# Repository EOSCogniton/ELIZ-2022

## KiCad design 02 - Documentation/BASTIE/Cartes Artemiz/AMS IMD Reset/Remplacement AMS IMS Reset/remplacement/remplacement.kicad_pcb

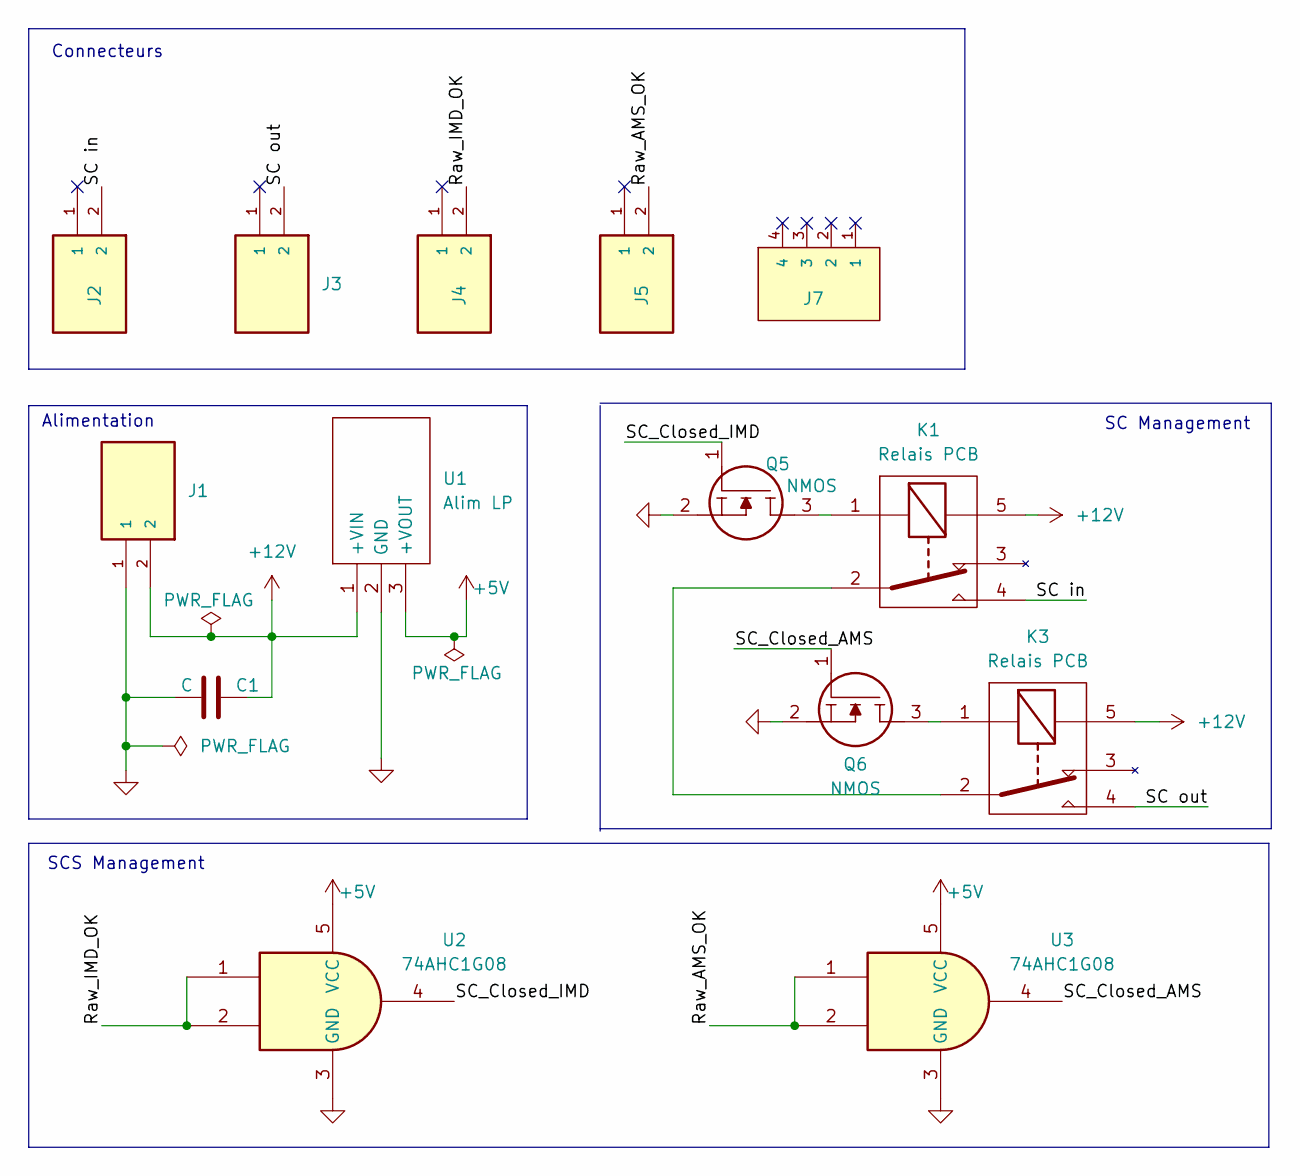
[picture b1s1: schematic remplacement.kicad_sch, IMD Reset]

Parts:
C1: C; CP_Radial_D5.0mm_P2.00mm
J1, J2, J3, J4, J5: 2P Droit 2-11-2022; MOLEX_22-11-2022; PARTREV BD8; Mouser Part Number 538-22-11-2022
J7: 4P Droit 22-11-2042; MOLEX_22-11-2042; Manufacturer_Part_Number 22-11-2042; Mouser Part Number 538-22-11-2042
K1, K3: Relais PCB; CP112V; Mouser Part Number 769-CP1-12V
Q5, Q6: NMOS SQ2348ES-T1_GE3; SOT95P237X112-3N; Manufacturer_Part_Number SQ2348ES-T1_GE3; Mouser Part Number 781-SQ2348ES-T1_GE3
U1: Alim LP TSR_0.5-2450; TSR-0.5-2433; Manufacturer_Part_Number TSR 0.5-2450; Mouser Part Number 495-TSR0.5-2450
U2, U3: 74AHC1G08; SOT-23-5_L3.0-W1.7-P0.95-LS2.8-BL

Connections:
+5V: U1.3 (+VOUT), U2.5 (VCC), U3.5 (VCC)
+12V: C1.2, J1.2, K1.5, K3.5, U1.1 (+VIN)
/Raw_AMS_OK: J5.2, U3.1, U3.2
/Raw_IMD_OK: J4.2, U2.1, U2.2
/SC in: J2.2, K1.4
/SC out: J3.2, K3.4
/SC_Closed_AMS: Q6.1, U3.4
/SC_Closed_IMD: Q5.1, U2.4
GND: C1.1, J1.1, Q5.2, Q6.2, U1.2 (GND), U2.3 (GND), U3.3 (GND)
unnamed: K1.1, Q5.3
unnamed: K1.2, K3.2
unnamed: K3.1, Q6.3

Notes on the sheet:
Alimentation
SC Management
SCS Management
Connecteurs

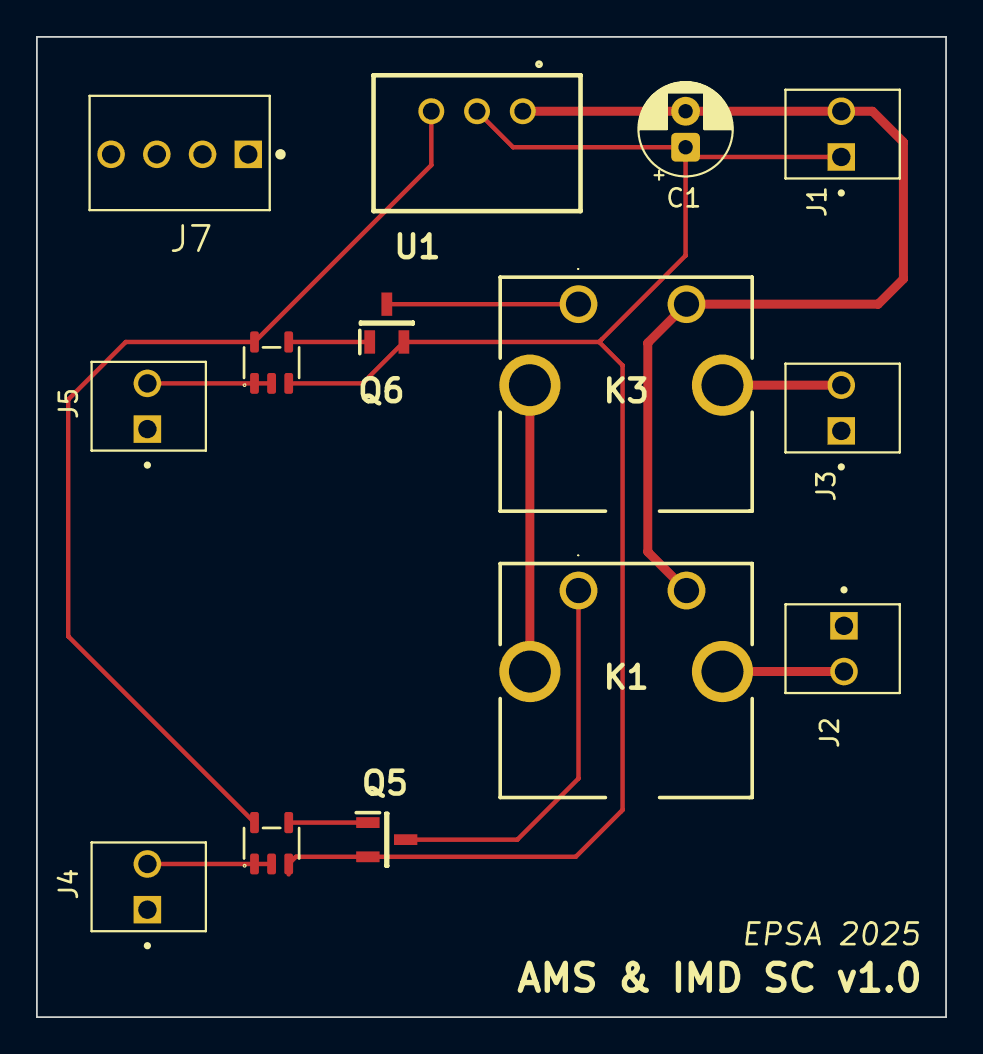
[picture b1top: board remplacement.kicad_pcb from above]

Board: 2 copper layers, 50.5 x 54.5 mm, 14 parts (0 on the bottom side), 12 nets.

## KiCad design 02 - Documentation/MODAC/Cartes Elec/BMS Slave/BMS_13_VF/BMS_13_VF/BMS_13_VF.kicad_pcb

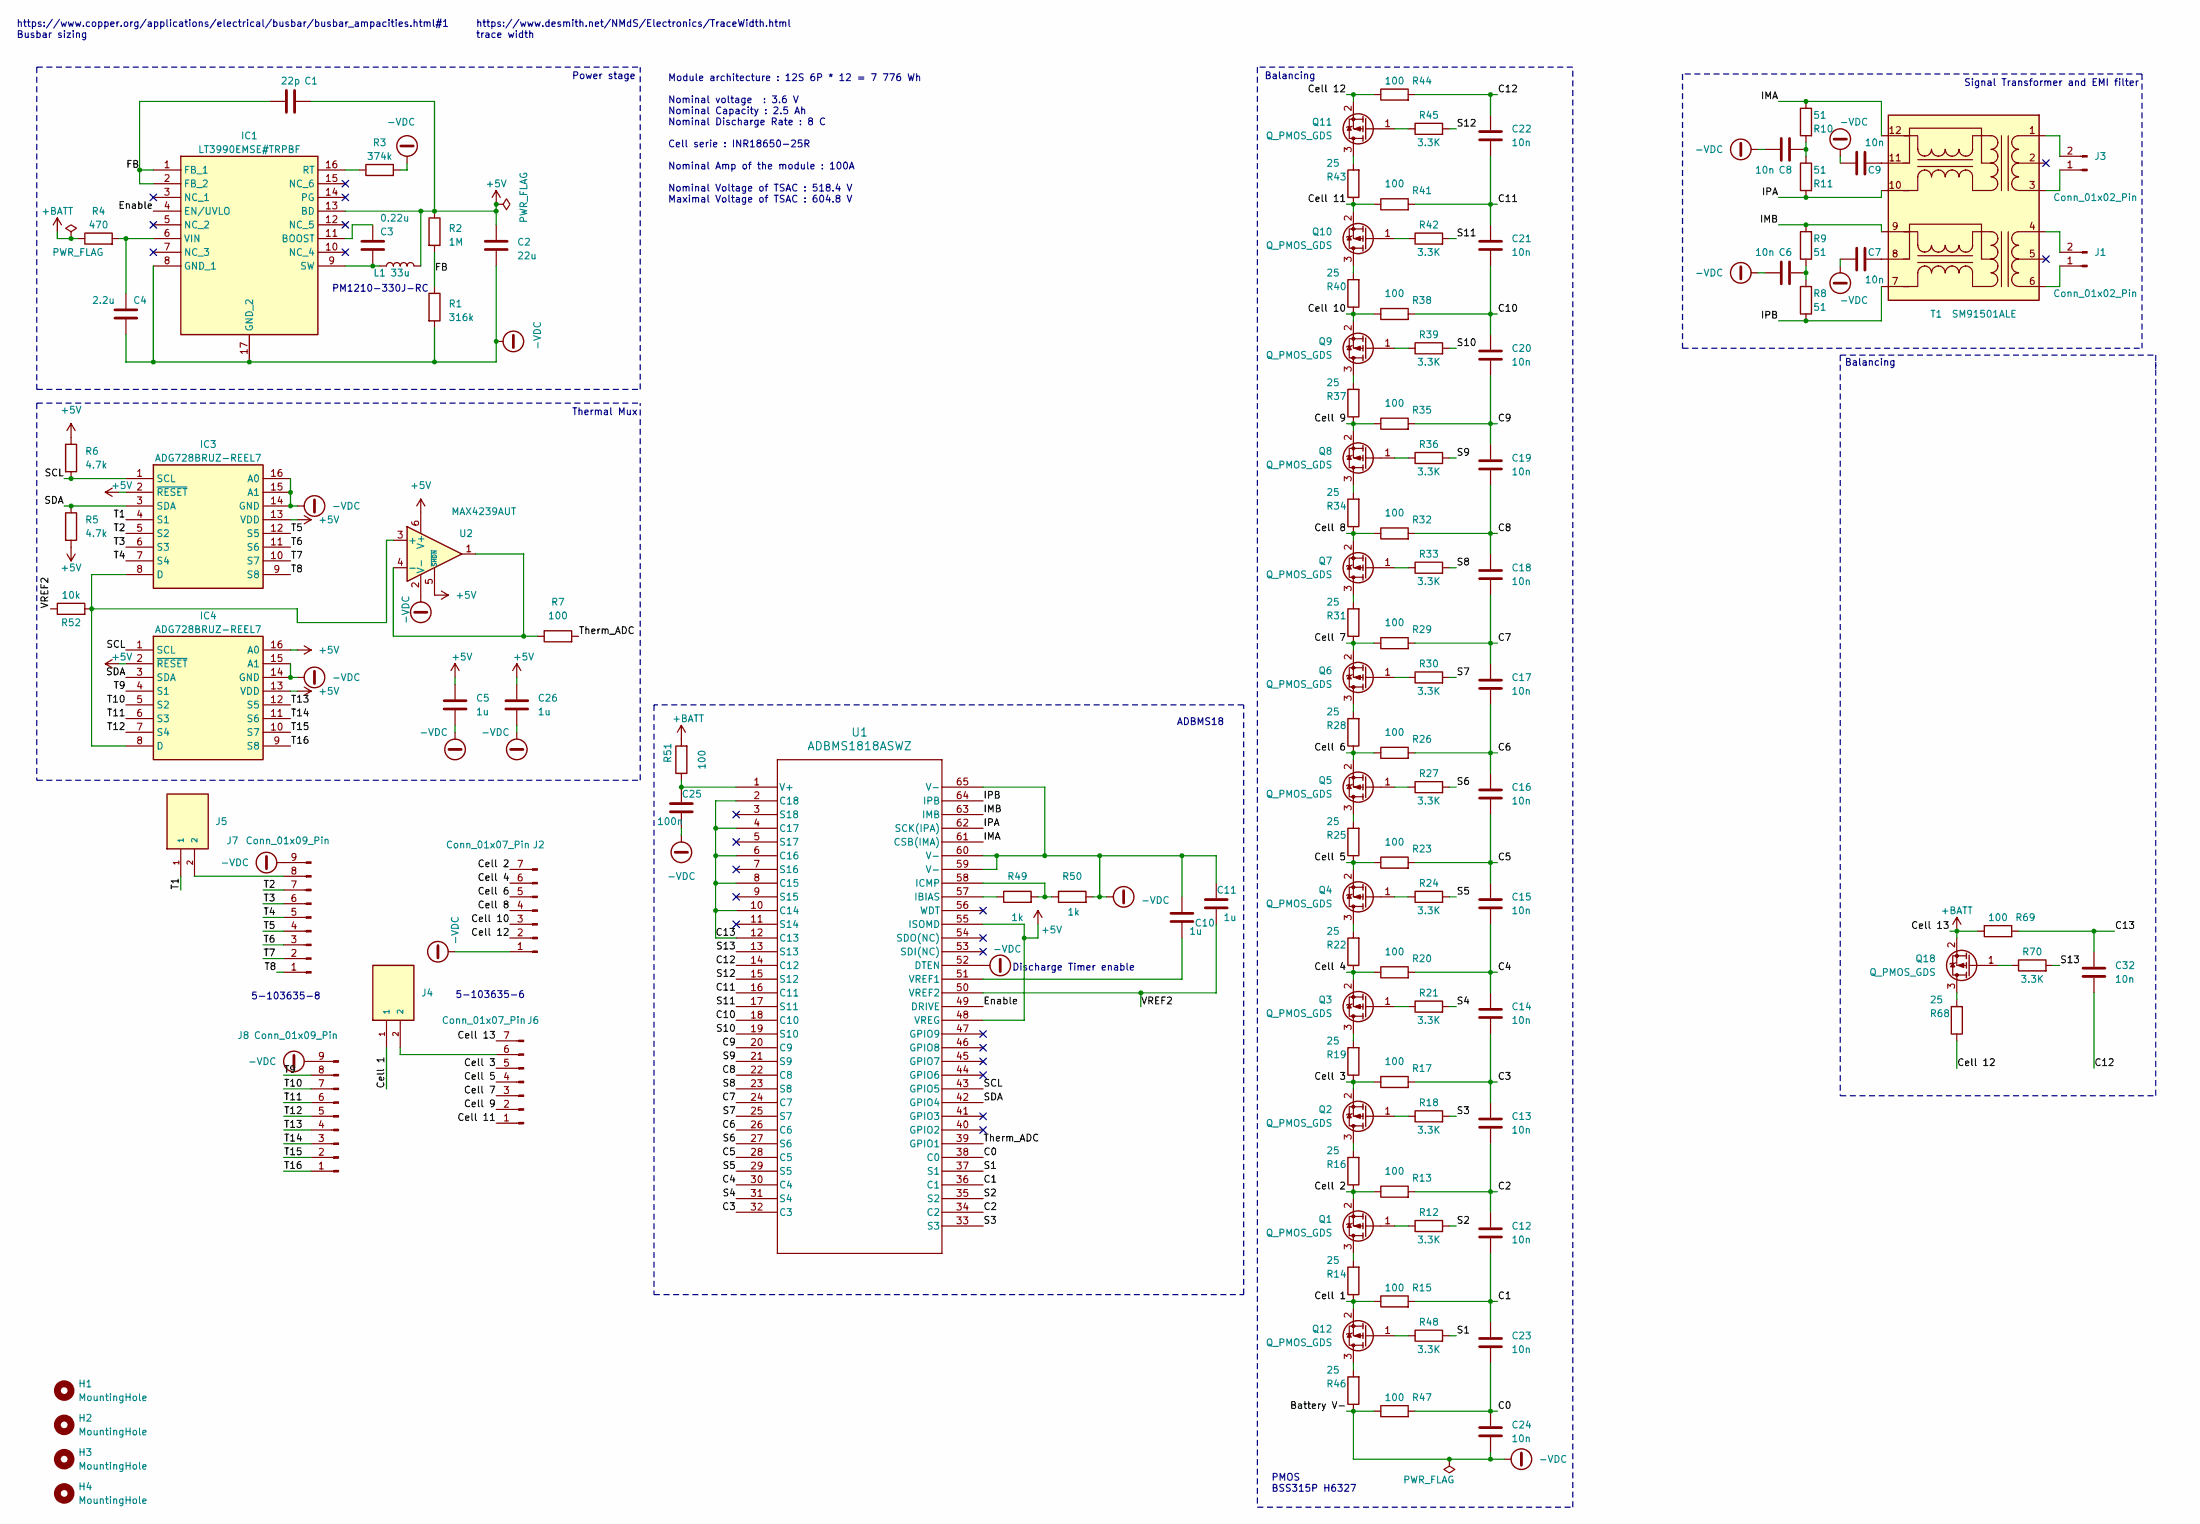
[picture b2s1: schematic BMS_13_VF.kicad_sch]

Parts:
C1: 22p; C_0805_2012Metric_Pad1.18x1.45mm_HandSolder
C2: 22u; C_0805_2012Metric_Pad1.18x1.45mm_HandSolder
C3: 0.22u; C_0805_2012Metric_Pad1.18x1.45mm_HandSolder
C4: 2.2u; C_0805_2012Metric_Pad1.18x1.45mm_HandSolder
C5, C10, C11, C26: 1u; C_0805_2012Metric_Pad1.18x1.45mm_HandSolder
C6, C7, C8, C9, C12, C13, C14, C15, C16, C17, C18, C19, C20, C21, C22, C23, C24, C32: 10n; C_0805_2012Metric_Pad1.18x1.45mm_HandSolder
C25: 100n; C_0805_2012Metric_Pad1.18x1.45mm_HandSolder
H1, H2, H3, H4: MountingHole; MountingHole_3.2mm_M3_DIN965_Pad
IC1: LT3990EMSE#TRPBF; SOP50P490X110-17N; Mouser Part Number 584-LT3990EMSE#TRPBF
IC3, IC4: ADG728BRUZ-REEL7; SOP65P640X120-16N; Mouser Part Number 584-ADG728BRUZ-R7
J1, J3: Conn_01x02_Pin; RHDR2W97P0X254_1X2_654X508X1379P
J2, J6: Conn_01x07_Pin; SHDRRA7W77P0X254_1X7_2032X1359X699P
J4, J5: 2P Droit 22-11-2022; MOLEX_22-11-2022; PARTREV BD8; Mouser Part Number 538-22-11-2022
J7, J8: Conn_01x09_Pin; SHDRRA9W69P0X254_1X9_2527X1359X741P
L1: 33u; L_1210_3225Metric_Pad1.42x2.65mm_HandSolder
Q1, Q2, Q3, Q4, Q5, Q6, Q7, Q8, Q9, Q10, Q11, Q12: Q_PMOS_GDS; SOT-23-3
Q18: Q_PMOS_GDS; SOT95P237X112-3N
R1: 316k; R_1206_3216Metric_Pad1.30x1.75mm_HandSolder
R2: 1M; R_1206_3216Metric_Pad1.30x1.75mm_HandSolder
R3: 374k; R_1206_3216Metric_Pad1.30x1.75mm_HandSolder
R4: 470; R_1206_3216Metric_Pad1.30x1.75mm_HandSolder
R5, R6: 4.7k; R_1206_3216Metric_Pad1.30x1.75mm_HandSolder
R7, R13, R15, R17, R20, R23, R26, R29, R32, R35, R38, R41, R44, R47, R51, R69: 100; R_1206_3216Metric_Pad1.30x1.75mm_HandSolder
R8, R9, R10, R11: 51; R_1206_3216Metric_Pad1.30x1.75mm_HandSolder
R12, R18, R21, R24, R27, R30, R33, R36, R39, R42, R45, R48, R70: 3.3K; R_1206_3216Metric_Pad1.30x1.75mm_HandSolder
R14, R16, R19, R22, R25, R28, R31, R34, R37, R40, R43, R46, R68: 25; R_2512_6332Metric_Pad1.40x3.35mm_HandSolder
R49, R50: 1k; R_1206_3216Metric_Pad1.30x1.75mm_HandSolder
R52: 10k; R_1206_3216Metric_Pad1.30x1.75mm_HandSolder
T1: SM91501ALE; SOP200P1473X500-12N; Mouser Part Number 652-SM91501ALE
U1: ADBMS1818ASWZ; 05-08-1982_ADI
U2: MAX4239AUT; SOT-23-6

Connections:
+5V: C1.2, C2.2, C5.1, C26.1, IC1.13 (BD), IC3.2 (~RESET), IC3.13 (VDD), IC4.2 (~RESET), IC4.13 (VDD), IC4.16 (A0), L1.2, R2.1, R5.2, R6.1, U1.48 (VREG), U1.55 (ISOMD), U2.5 (~SHDN), U2.6 (V+)
+BATT: J6.7, Q18.2 (S), R4.1, R51.2, R69.1
-VDC: C2.1, C4.1, C5.2, C6.1, C7.1, C8.1, C9.1, C10.1, C11.1, C24.2, C25.2, C26.2, IC1.8 (GND_1), IC1.17 (GND_2), IC3.14 (GND), IC3.15 (A1), IC3.16 (A0), IC4.14 (GND), IC4.15 (A1), J2.1, J7.9, J8.9, R1.2, R3.2, R46.1, R47.1, R50.2, U1.52 (DTEN), U1.59 (V-), U1.60 (V-), U1.65 (V-), U2.2 (V-)
/C0: C23.2, C24.1, R47.2, U1.38 (C0)
/C1: C12.2, C23.1, R15.2, U1.36 (C1)
/C2: C12.1, C13.2, R13.2, U1.34 (C2)
/C3: C13.1, C14.2, R17.2, U1.32 (C3)
/C4: C14.1, C15.2, R20.2, U1.30 (C4)
/C5: C15.1, C16.2, R23.2, U1.28 (C5)
/C6: C16.1, C17.2, R26.2, U1.26 (C6)
/C7: C17.1, C18.2, R29.2, U1.24 (C7)
/C8: C18.1, C19.2, R32.2, U1.22 (C8)
/C9: C19.1, C20.2, R35.2, U1.20 (C9)
/C10: C20.1, C21.2, R38.2, U1.18 (C10)
/C11: C21.1, C22.2, R41.2, U1.16 (C11)
/C12: C22.1, C32.2, R44.2, U1.14 (C12)
/C13: C32.1, R69.2, U1.2 (C18), U1.4 (C17), U1.6 (C16), U1.8 (C15), U1.10 (C14), U1.12 (C13)
/Cell 1: J4.1, Q12.2 (S), R14.1, R15.1
/Cell 2: J2.7, Q1.2 (S), R13.1, R16.1
/Cell 3: J6.5, Q2.2 (S), R17.1, R19.1
/Cell 4: J2.6, Q3.2 (S), R20.1, R22.1
/Cell 5: J6.4, Q4.2 (S), R23.1, R25.1
/Cell 6: J2.5, Q5.2 (S), R26.1, R28.1
/Cell 7: J6.3, Q6.2 (S), R29.1, R31.1
/Cell 8: J2.4, Q7.2 (S), R32.1, R34.1
/Cell 9: J6.2, Q8.2 (S), R35.1, R37.1
/Cell 10: J2.3, Q9.2 (S), R38.1, R40.1
/Cell 11: J6.1, Q10.2 (S), R41.1, R43.1
/Cell 12: J2.2, Q11.2 (S), R44.1, R68.1
/Enable: IC1.4 (EN/UVLO), U1.49 (DRIVE)
/FB: C1.1, IC1.1 (FB_1), IC1.2 (FB_2), R1.1, R2.2
/IMA: R10.1, T1.12 (SEC1_3), U1.61 (CSB(IMA))
/IMB: R9.2, T1.9 (SEC2_3), U1.63 (IMB)
/IPA: R11.2, T1.10 (SEC1_1), U1.62 (SCK(IPA))
/IPB: R8.1, T1.7 (SEC2_1), U1.64 (IPB)
/S1: R48.2, U1.37 (S1)
/S2: R12.2, U1.35 (S2)
/S3: R18.2, U1.33 (S3)
/S4: R21.2, U1.31 (S4)
/S5: R24.2, U1.29 (S5)
/S6: R27.2, U1.27 (S6)
/S7: R30.2, U1.25 (S7)
/S8: R33.2, U1.23 (S8)
/S9: R36.2, U1.21 (S9)
/S10: R39.2, U1.19 (S10)
/S11: R42.2, U1.17 (S11)
/S12: R45.2, U1.15 (S12)
/S13: R70.2, U1.13 (S13)
/SCL: IC3.1 (SCL), IC4.1 (SCL), R6.2, U1.43 (GPIO5)
/SDA: IC3.3 (SDA), IC4.3 (SDA), R5.1, U1.42 (GPIO4)
/T1: IC3.4 (S1), J5.1
/T2: IC3.5 (S2), J7.7
/T3: IC3.6 (S3), J7.6
/T4: IC3.7 (S4), J7.5
/T5: IC3.12 (S5), J7.4
/T6: IC3.11 (S6), J7.3
/T7: IC3.10 (S7), J7.2
/T8: IC3.9 (S8), J7.1
/T9: IC4.4 (S1), J8.8
/T10: IC4.5 (S2), J8.7
/T11: IC4.6 (S3), J8.6
/T12: IC4.7 (S4), J8.5
/T13: IC4.12 (S5), J8.4
/T14: IC4.11 (S6), J8.3
/T15: IC4.10 (S7), J8.2
/T16: IC4.9 (S8), J8.1
/Therm_ADC: R7.2, U1.39 (GPIO1)
/VREF2: C11.2, R52.1, U1.50 (VREF2)
unnamed: C6.2, R8.2, R9.1
unnamed: C8.2, R10.2, R11.1
unnamed: C3.2, IC1.11 (BOOST)
unnamed: IC1.16 (RT), R3.1
unnamed: C3.1, IC1.9 (SW), L1.1
unnamed: C4.2, IC1.6 (VIN), R4.2
unnamed: IC3.8 (D), IC4.8 (D), R52.2, U2.3 (+)
unnamed: J1.1, T1.6 (PRI2_3)
unnamed: J1.2, T1.4 (PRI2_1)
unnamed: J3.1, T1.3 (PRI1_3)
unnamed: J3.2, T1.1 (PRI1_1)
unnamed: J4.2, J6.6
unnamed: J5.2, J7.8
unnamed: Q1.3 (D), R14.2
unnamed: Q1.1 (G), R12.1
unnamed: Q2.3 (D), R16.2
unnamed: Q2.1 (G), R18.1
unnamed: Q3.3 (D), R19.2
unnamed: Q3.1 (G), R21.1
unnamed: Q4.3 (D), R22.2
unnamed: Q4.1 (G), R24.1
unnamed: Q5.3 (D), R25.2
unnamed: Q5.1 (G), R27.1
unnamed: Q6.3 (D), R28.2
unnamed: Q6.1 (G), R30.1
unnamed: Q7.3 (D), R31.2
unnamed: Q7.1 (G), R33.1
unnamed: Q8.3 (D), R34.2
unnamed: Q8.1 (G), R36.1
unnamed: Q9.3 (D), R37.2
unnamed: Q9.1 (G), R39.1
unnamed: Q10.3 (D), R40.2
unnamed: Q10.1 (G), R42.1
unnamed: Q11.3 (D), R43.2
unnamed: Q11.1 (G), R45.1
unnamed: Q12.3 (D), R46.2
unnamed: Q12.1 (G), R48.1
unnamed: Q18.3 (D), R68.2
unnamed: Q18.1 (G), R70.1
unnamed: C9.2, T1.11 (SEC1_2)
unnamed: C7.2, T1.8 (SEC2_2)
unnamed: R49.1, U1.57 (IBIAS)
unnamed: R49.2, R50.1, U1.58 (ICMP)
unnamed: C25.1, R51.1, U1.1 (V+)
unnamed: C10.2, U1.51 (VREF1)
unnamed: R7.1, U2.1, U2.4 (-)

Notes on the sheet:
Module architecture : 12S 6P * 12 = 7 776 Wh Nominal voltage : 3.6 V Nominal Capacity : 2.5 Ah Nominal Discharge Rate : 8 C Cell serie : INR18650-25R Nominal Amp of the module : 100A Nominal Voltage of TSAC : 518.4 V Maximal Voltage of TSAC : 604.8 V
PMOS BSS315P H6327
PM1210-330J-RC
Balancing
Thermal Mux
Power stage
Signal Transformer and EMI filter
ADBMS18
https://www.desmith.net/NMdS/Electronics/TraceWidth.html trace width
5-103635-8
https://www.copper.org/applications/electrical/busbar/busbar_ampacities.html#1 Busbar sizing
5-103635-6
Discharge Timer enable

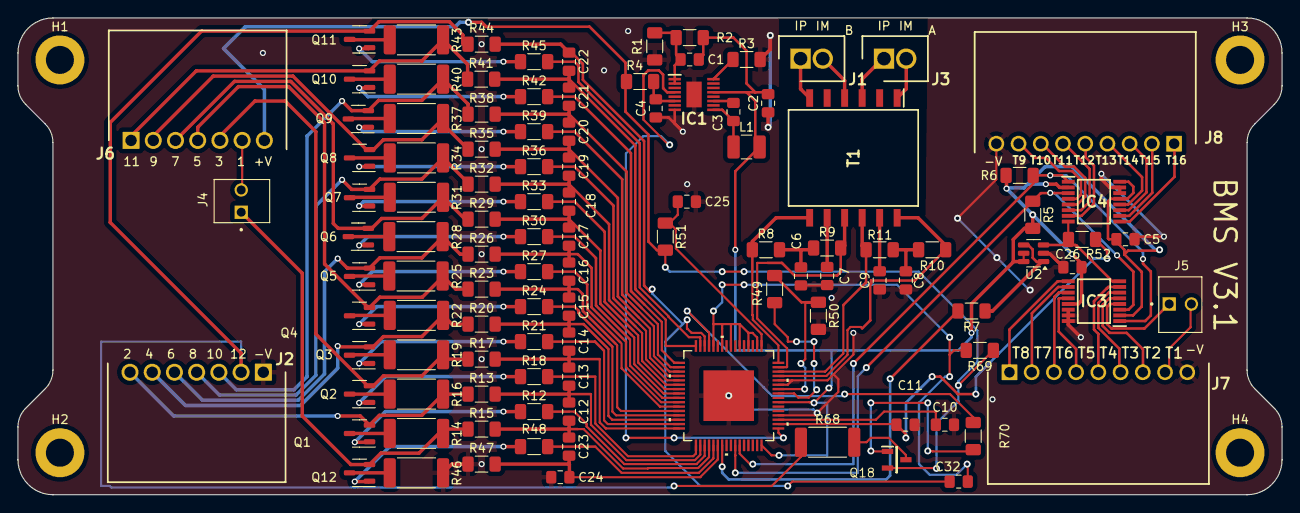
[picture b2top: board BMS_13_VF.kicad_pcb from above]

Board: 2 copper layers, 144.5 x 54.5 mm, 114 parts (0 on the bottom side), 114 nets.

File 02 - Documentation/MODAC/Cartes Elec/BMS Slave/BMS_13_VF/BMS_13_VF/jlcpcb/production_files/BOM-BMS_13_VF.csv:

Comment,Designator,Footprint,LCSC,Quantity
Q_PMOS_GDS,"Q1,Q10,Q11,Q12,Q18,Q2,Q3,Q4,Q5,Q6,Q7,Q8,Q9",SOT-23-3,C10487,13
25,"R14,R16,R19,R22,R25,R28,R31,R34,R37,R40,R43,R46,R68",R_2512_6332Metric_Pad1.40x3.35mm_HandSolder,C107659,13
10n,"C12,C13,C14,C15,C16,C17,C18,C19,C20,C21,C22,C23,C24,C32,C6,C7,C8,C9",C_0805_2012Metric_Pad1.18x1.45mm_HandSolder,C1710,18
100,"R13,R15,R17,R20,R23,R26,R29,R32,R35,R38,R41,R44,R47,R51,R69,R7",R_1206_3216Metric_Pad1.30x1.75mm_HandSolder,C17901,16
10k,R52,R_1206_3216Metric_Pad1.30x1.75mm_HandSolder,C17902,1
1M,R2,R_1206_3216Metric_Pad1.30x1.75mm_HandSolder,C17927,1
4.7k,"R5,R6",R_1206_3216Metric_Pad1.30x1.75mm_HandSolder,C17936,2
51,"R10,R11,R8,R9",R_1206_3216Metric_Pad1.30x1.75mm_HandSolder,C18019,4
22p,C1,C_0805_2012Metric_Pad1.18x1.45mm_HandSolder,C1804,1
316k,R1,R_1206_3216Metric_Pad1.30x1.75mm_HandSolder,C247297,1
33u,L1,L_1210_3225Metric_Pad1.42x2.65mm_HandSolder,C250234,1
3.3K,"R12,R18,R21,R24,R27,R30,R33,R36,R39,R42,R45,R48,R70",R_1206_3216Metric_Pad1.30x1.75mm_HandSolder,C26032,13
100n,C25,C_0805_2012Metric_Pad1.18x1.45mm_HandSolder,C28233,1
1u,"C10,C11,C26,C5",C_0805_2012Metric_Pad1.18x1.45mm_HandSolder,C28323,4
374k,R3,R_1206_3216Metric_Pad1.30x1.75mm_HandSolder,C2984514,1
ADBMS1818ASWZ,U1,05-08-1982_ADI,C3682393,1
2.2u,C4,C_0805_2012Metric_Pad1.18x1.45mm_HandSolder,C377773,1
1k,"R49,R50",R_1206_3216Metric_Pad1.30x1.75mm_HandSolder,C4410,2
470,R4,R_1206_3216Metric_Pad1.30x1.75mm_HandSolder,C4502,1
22u,C2,C_0805_2012Metric_Pad1.18x1.45mm_HandSolder,C45783,1
MAX4239AUT,U2,SOT-23-6,C479740,1
0.22u,C3,C_0805_2012Metric_Pad1.18x1.45mm_HandSolder,C5378,1
ADG728BRUZ-REEL7,"IC3,IC4",SOP65P640X120-16N,C579101,2
LT3990EMSE#TRPBF,IC1,SOP50P490X110-17N,C580168,1
SM91501ALE,T1,SOP200P1473X500-12N,,1

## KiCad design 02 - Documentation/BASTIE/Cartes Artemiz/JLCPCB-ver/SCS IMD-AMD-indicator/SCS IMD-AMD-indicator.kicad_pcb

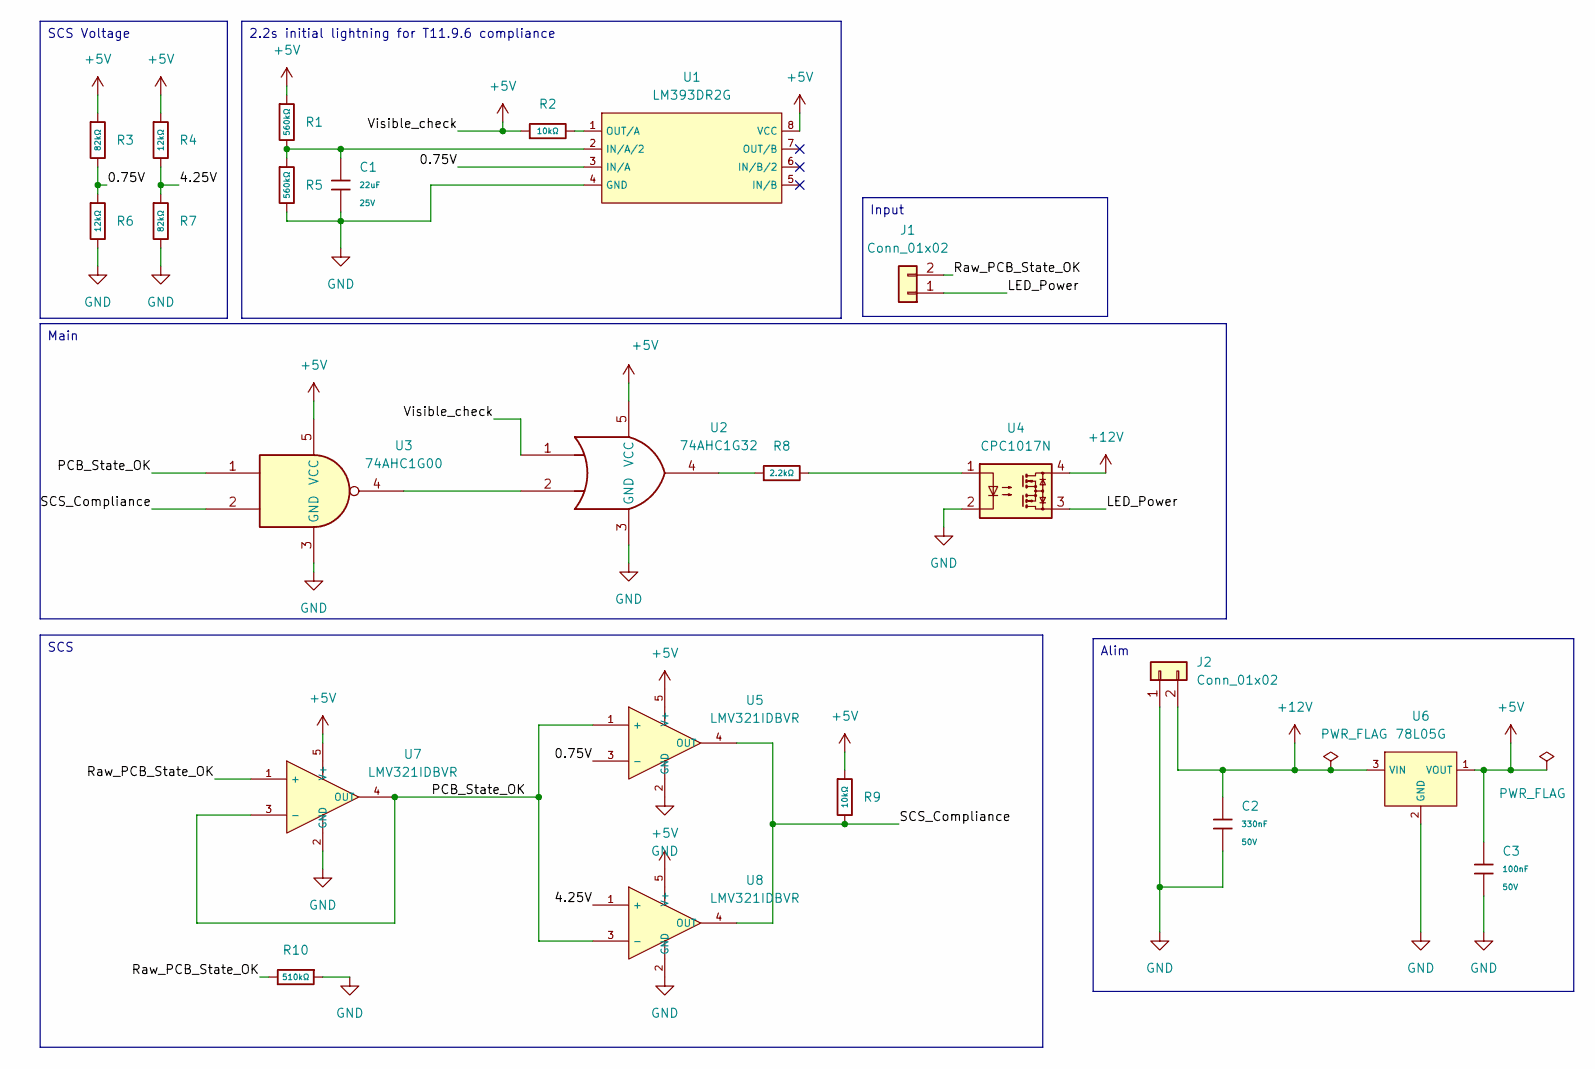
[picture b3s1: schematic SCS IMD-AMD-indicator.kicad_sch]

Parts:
C1: 22uF; C_0805; Voltage Rated 25V; Tolerance ±20%; Part CL21A226MAQNNNE; LCSC C45783
C2: 330nF; C_0805; Voltage Rated 50V; Tolerance ±10%; Part 0805B334K500NT; LCSC C1740
C3: 100nF; C_0805; Voltage Rated 50V; Tolerance ±10%; Part CC0805KRX7R9BB104; LCSC C49678
J1, J2: Conn_01x02; Molex_KK-254_AE-6410-02A_1x02_P2.54mm_Vertical
R1, R5: 560kΩ; R_0603; Overload Voltage (Max) 75V; Tolerance ±1%; Part 0603WAF5603T5E; LCSC C23203
R2, R9: 10kΩ; R_0805; Overload Voltage (Max) 150V; Tolerance ±1%; Part 0805W8F1002T5E; LCSC C17414
R3, R7: 82kΩ; R_0805; Overload Voltage (Max) 150V; Tolerance ±1%; Part 0805W8F8202T5E; LCSC C17840
R4, R6: 12kΩ; R_0805; Overload Voltage (Max) 150V; Tolerance ±1%; Part 0805W8F1202T5E; LCSC C17444
R8: 2.2kΩ; R_0805; Overload Voltage (Max) 150V; Tolerance ±1%; Part 0805W8F2201T5E; LCSC C17520
R10: 510kΩ; R_0805; Overload Voltage (Max) 150V; Tolerance ±1%; Part 0805W8F5103T5E; LCSC C17733
U1: LM393DR2G; SOIC-8_L5.0-W4.0-P1.27-LS6.0-BL; Supply Voltage 2V~36V;1V~18V; Part LM393DR2G; LCSC C7955
U2: 74AHC1G32; SC-74A-5_1.55x2.9mm_P0.95mm
U3: 74AHC1G00; SOT-23-5_L3.0-W1.7-P0.95-LS2.8-BR
U4: CPC1017N; SOP-4_3.8x4.1mm_P2.54mm
U5, U7, U8: LMV321IDBVR; SOT-23-5_L3.0-W1.7-P0.95-LS2.8-BR; Part LMV321IDBVR; LCSC C7972
U6: 78L05G; SOT-89-3_L4.5-W2.5-P1.50-LS4.2-BR; Output Voltage 5V; Dropout Voltage 1.7V@(40mA); Part 78L05G-AB3-R; LCSC C71136

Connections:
+5V: C3.1, R1.1, R2.1, R3.1, R4.1, R9.1, U1.8 (VCC), U2.1, U2.5 (VCC), U3.5 (VCC), U5.5 (V+), U6.1 (VOUT), U7.5 (V+), U8.5 (V+)
+12V: C2.1, J2.2, U4.4, U6.3 (VIN)
/0.75V: R3.2, R6.1, U1.3 (IN/A), U5.3 (-)
/4.25V: R4.2, R7.1, U8.1 (+)
/LED_Power: J1.1, U4.3
/PCB_State_OK: U3.1, U5.1 (+), U7.3 (-), U7.4 (OUT), U8.3 (-)
/Raw_PCB_State_OK: J1.2, R10.2, U7.1 (+)
/SCS_Compliance: R9.2, U3.2, U5.4 (OUT), U8.4 (OUT)
GND: C1.2, C2.2, C3.2, J2.1, R5.2, R6.2, R7.2, R10.1, U1.4 (GND), U2.3 (GND), U3.3 (GND), U4.2, U5.2 (GND), U6.2 (GND), U7.2 (GND), U8.2 (GND)
unnamed: R8.1, U2.4
unnamed: R8.2, U4.1
unnamed: C1.1, R1.2, R5.1, U1.2 (IN/A/2)
unnamed: R2.2, U1.1 (OUT/A)
unnamed: U2.2, U3.4

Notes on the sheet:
Main
Input
2.2s initial lightning for T11.9.6 compliance
SCS Voltage
Alim
SCS

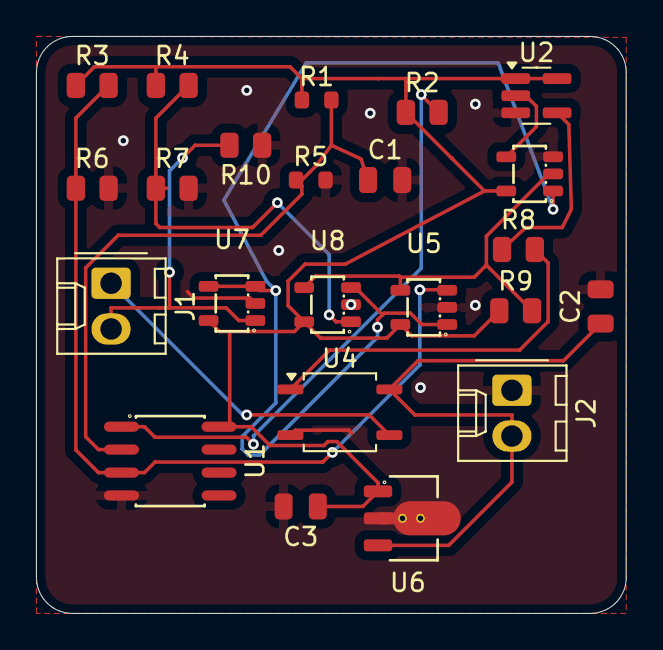
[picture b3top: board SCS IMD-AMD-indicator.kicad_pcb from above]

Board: 2 copper layers, 32.8 x 32.1 mm, 23 parts (0 on the bottom side), 14 nets.

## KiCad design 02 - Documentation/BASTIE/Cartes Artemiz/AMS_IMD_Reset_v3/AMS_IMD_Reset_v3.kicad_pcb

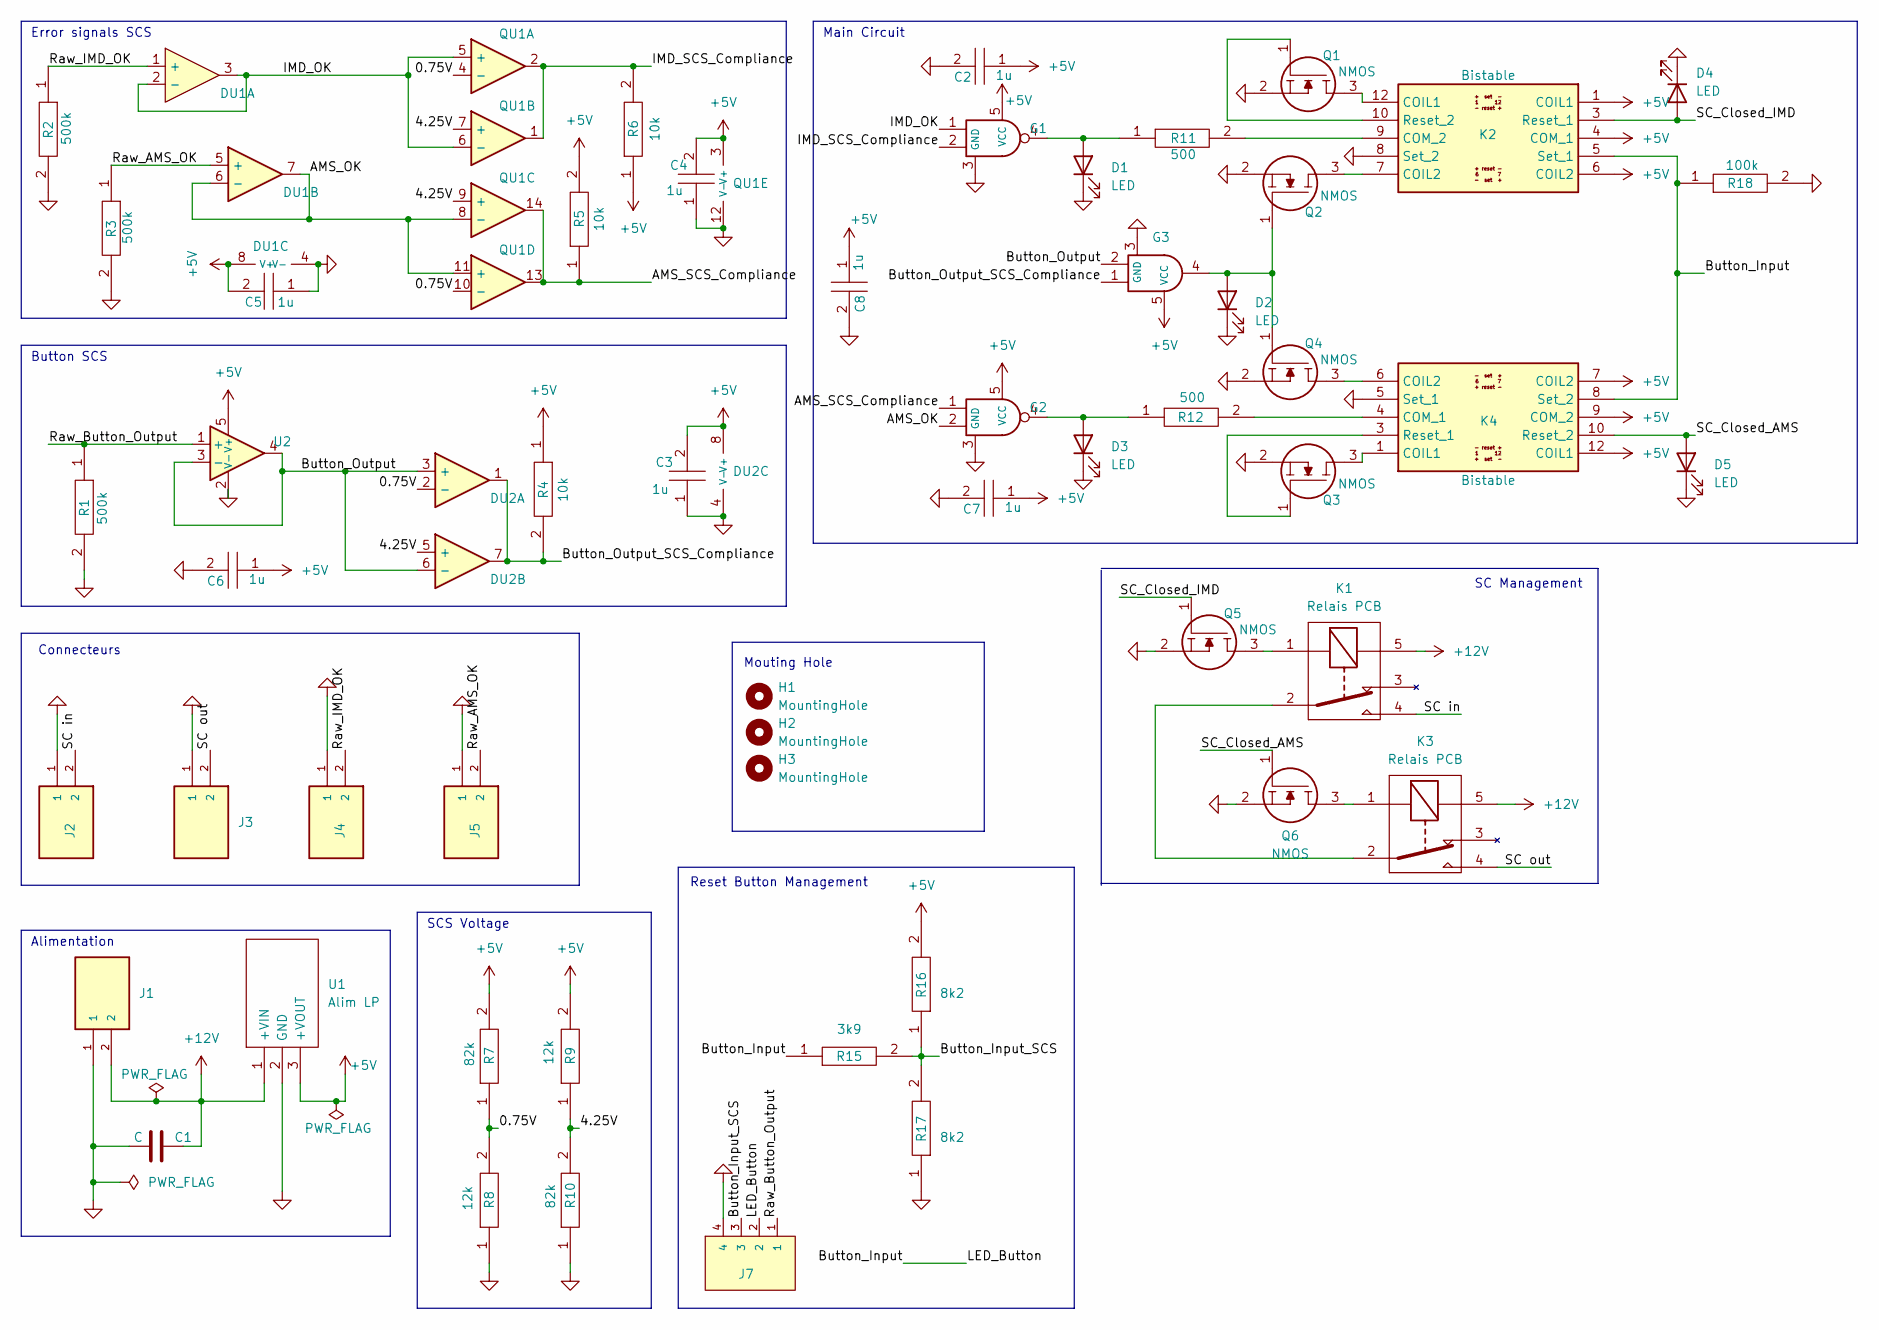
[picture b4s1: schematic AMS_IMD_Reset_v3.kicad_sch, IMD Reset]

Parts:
C1: C; CP_Radial_D5.0mm_P2.00mm
C2, C3, C4, C5, C6, C7, C8: 1u; CAPC2012X130N; Manufacturer_Part_Number 0805Y1000104JXT
D1, D2, D3, D4, D5: LED; LED_D5.0mm
DU1: Opamp_Dual; TSSOP-8_4.4x3mm_P0.65mm; Manufacturer_Part_Number TLV9062QPWRQ1; Mouser Part Number 595-TLV9062QPWRQ1
DU2: Opamp_Dual; TSSOP-8_4.4x3mm_P0.65mm; Manufacturer_Part_Number LMV393IPWR; Mouser Part Number 595-LMV393IPWR
G1, G2: Gate NAND SN74AHCT1G00DBVR; SOT95P280X145-5N; Manufacturer_Part_Number SN74AHCT1G00DBVR; Mouser Part Number 595-SN74AHCT1G00DBVR
G3: Gate AND SN74AHCT1G08DBVR; SOT95P280X145-5N; Manufacturer_Part_Number SN74AHCT1G08DBVR; Mouser Part Number 595-SN74AHCT1G08DBVR
H1, H2, H3: MountingHole; MountingHole_2.7mm_M2.5
J1, J2, J3, J4, J5: 2P Droit 2-11-2022; MOLEX_22-11-2022; PARTREV BD8; Mouser Part Number 538-22-11-2022
J7: 4P Droit 22-11-2042; MOLEX_22-11-2042; Manufacturer_Part_Number 22-11-2042; Mouser Part Number 538-22-11-2042
K1, K3: Relais PCB; CP112V; Mouser Part Number 769-CP1-12V
K2, K4: Bistable V23079B1201B301; V23079B1201B301; Mouser Part Number 655-V23079B1201B301
Q1, Q2, Q3, Q4, Q5, Q6: NMOS SQ2348ES-T1_GE3; SOT95P237X112-3N; Manufacturer_Part_Number SQ2348ES-T1_GE3; Mouser Part Number 781-SQ2348ES-T1_GE3
QU1: Opamp_Quad; TSSOP-14_4.4x5mm_P0.65mm; Manufacturer_Part_Number LMV339IPWR; Mouser Part Number 595-LMV339IPWR
R1, R2, R3: 500k; RESC3216X70N; Manufacturer_Part_Number RK73H2BLTDD2152F; Mouser Part Number N/A
R4, R5, R6: 10k; RESC3216X70N; Manufacturer_Part_Number RK73H2BLTDD2152F; Mouser Part Number N/A
R7, R10: 82k; RESC3216X70N; Manufacturer_Part_Number RK73H2BLTDD2152F; Mouser Part Number N/A
R8, R9: 12k; RESC3216X70N; Manufacturer_Part_Number RK73H2BLTDD2152F; Mouser Part Number N/A
R11, R12: 500; RESC3216X70N; Manufacturer_Part_Number RK73H2BLTDD2152F; Mouser Part Number N/A
R15: 3k9; RESC3216X70N; Manufacturer_Part_Number RK73H2BLTDD2152F; Mouser Part Number N/A
R16, R17: 8k2; RESC3216X70N; Manufacturer_Part_Number RK73H2BLTDD2152F; Mouser Part Number N/A
R18: 100k; RESC3216X70N; Manufacturer_Part_Number RK73H2BLTDD2152F; Mouser Part Number N/A
U1: Alim LP TSR_0.5-2450; TSR-0.5-2433; Manufacturer_Part_Number TSR 0.5-2450; Mouser Part Number 495-TSR0.5-2450
U2: ${SIM.PARAMS}; SOT-353_SC-70-5_Handsoldering; Manufacturer_Part_Number TLV9061QDCKRQ1; Mouser Part Number 595-TLV9061QDCKRQ1

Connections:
+5V: C2.1, C3.2, C4.2, C5.2, C6.1, C7.1, C8.1, DU1.8 (V+), DU2.8 (V+), G1.5 (VCC), G2.5 (VCC), G3.5 (VCC), K2.1 (COIL1), K2.4 (COM_1), K2.6 (COIL2), K4.7 (COIL2), K4.9 (COM_2), K4.12 (COIL1), QU1.3 (V+), R4.1, R5.2, R6.1, R7.2, R9.2, R16.2, U1.3 (+VOUT), U2.5 (V+)
+12V: C1.2, J1.2, K1.5, K3.5, U1.1 (+VIN)
/0.75V: DU2.2 (-), QU1.4 (-), QU1.10 (-), R7.1, R8.2
/4.25V: DU2.5 (+), QU1.7 (+), QU1.9 (+), R9.1, R10.2
/AMS_OK: DU1.6 (-), DU1.7, G2.2, QU1.8 (-), QU1.11 (+)
/AMS_SCS_Compliance: G2.1, QU1.13, QU1.14, R5.1
/Button_Input: J7.2, K2.5 (Set_1), K4.8 (Set_2), R15.1, R18.1
/Button_Input_SCS: J7.3, R15.2, R16.1, R17.2
/Button_Output: DU2.3 (+), DU2.6 (-), G3.2, U2.3 (-), U2.4
/Button_Output_SCS_Compliance: DU2.1, DU2.7, G3.1, R4.2
/IMD_OK: DU1.2 (-), DU1.3, G1.1, QU1.5 (+), QU1.6 (-)
/IMD_SCS_Compliance: G1.2, QU1.1, QU1.2, R6.2
/Raw_AMS_OK: DU1.5 (+), J5.2, R3.1
/Raw_Button_Output: J7.1, R1.1, U2.1 (+)
/Raw_IMD_OK: DU1.1 (+), J4.2, R2.1
/SC in: J2.2, K1.4
/SC out: J3.2, K3.4
/SC_Closed_AMS: D5.2 (A), K4.10 (Reset_2), Q6.1
/SC_Closed_IMD: D4.2 (A), K2.3 (Reset_1), Q5.1
GND: C1.1, C2.2, C3.1, C4.1, C5.1, C6.2, C7.2, C8.2, D1.1 (K), D2.1 (K), D3.1 (K), D4.1 (K), D5.1 (K), DU1.4 (V-), DU2.4 (V-), G1.3 (GND), G2.3 (GND), G3.3 (GND), J1.1, J2.1, J3.1, J4.1, J5.1, J7.4, K2.8 (Set_2), K4.5 (Set_1), Q1.2, Q2.2, Q3.2, Q4.2, Q5.2, Q6.2, QU1.12 (V-), R1.2, R2.2, R3.2, R8.1, R10.1, R17.1, R18.2, U1.2 (GND), U2.2 (V-)
unnamed: D1.2 (A), G1.4, R11.1
unnamed: D2.2 (A), G3.4, Q2.1, Q4.1
unnamed: D3.2 (A), G2.4, R12.1
unnamed: K1.1, Q5.3
unnamed: K1.2, K3.2
unnamed: K2.12 (COIL1), Q1.3
unnamed: K2.7 (COIL2), Q2.3
unnamed: K2.9 (COM_2), R11.2
unnamed: K2.10 (Reset_2), Q1.1
unnamed: K3.1, Q6.3
unnamed: K4.1 (COIL1), Q3.3
unnamed: K4.6 (COIL2), Q4.3
unnamed: K4.4 (COM_1), R12.2
unnamed: K4.3 (Reset_1), Q3.1

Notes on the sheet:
Error signals SCS
Button SCS
Alimentation
SC Management
Main Circuit
Mouting Hole
Reset Button Management
SCS Voltage
Connecteurs

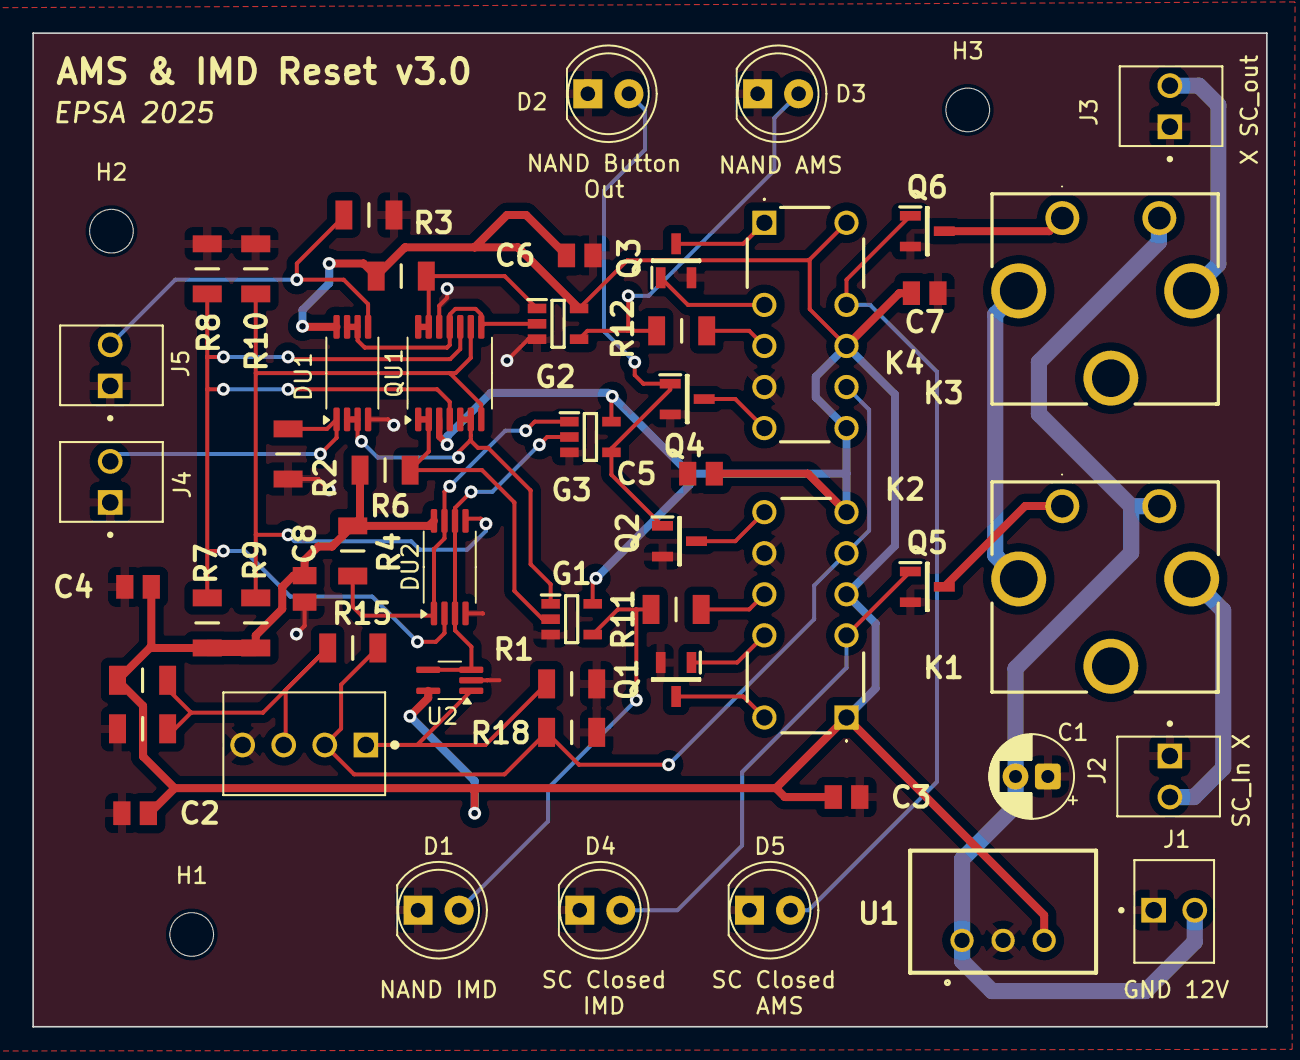
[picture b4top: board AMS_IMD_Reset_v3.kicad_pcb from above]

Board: 2 copper layers, 76.3 x 61.5 mm, 56 parts (0 on the bottom side), 34 nets.
